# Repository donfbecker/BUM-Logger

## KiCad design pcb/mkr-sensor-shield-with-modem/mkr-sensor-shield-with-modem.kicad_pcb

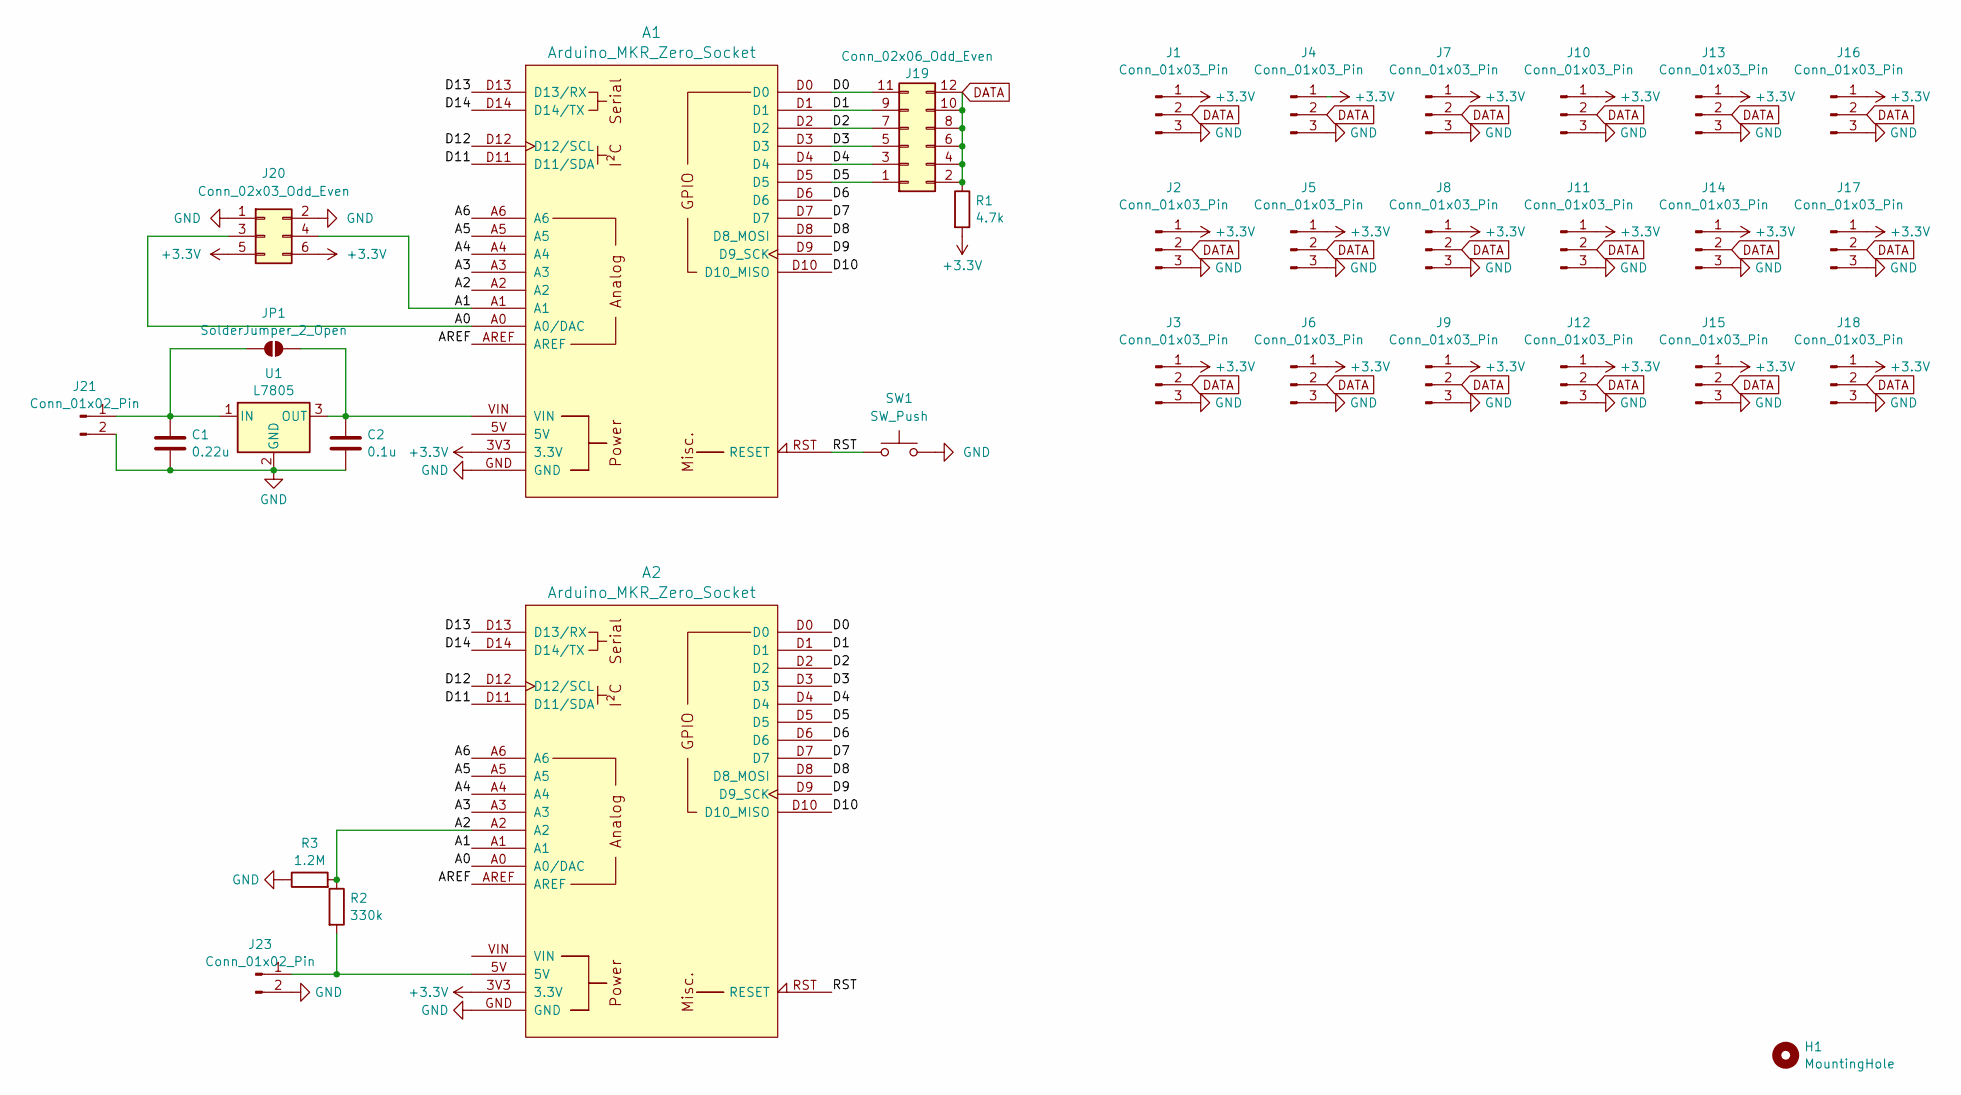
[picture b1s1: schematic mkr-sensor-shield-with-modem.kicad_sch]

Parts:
A1, A2: Arduino_MKR_Zero_Socket
C1: 0.22u; C_1206_3216Metric
C2: 0.1u; C_1206_3216Metric
H1: MountingHole; MountingHole_4.3mm_M4
J1, J2, J3, J4, J5, J6, J7, J8, J9, J10, J11, J12, J13, J14, J15, J16, J17, J18: Conn_01x03_Pin; JST_XH_B3B-XH-A_1x03_P2.50mm_Vertical
J19: Conn_02x06_Odd_Even; PinHeader_2x06_P2.54mm_Vertical
J20: Conn_02x03_Odd_Even; PinHeader_2x03_P2.54mm_Vertical
J21, J23: Conn_01x02_Pin; Power_Solder_Pads
JP1: SolderJumper_2_Open; SolderJumper-2_P1.3mm_Open_TrianglePad1.0x1.5mm
R1: 4.7k; R_Axial_DIN0207_L6.3mm_D2.5mm_P10.16mm_Horizontal
R2: 330k; R_Axial_DIN0207_L6.3mm_D2.5mm_P10.16mm_Horizontal
R3: 1.2M; R_Axial_DIN0207_L6.3mm_D2.5mm_P10.16mm_Horizontal
SW1: SW_Push; SW_PUSH_6mm
U1: L7805; SOT-223

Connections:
+3.3V: A1.3V3 (3.3V), A2.3V3 (3.3V), J1.1, J2.1, J3.1, J4.1, J5.1, J6.1, J7.1, J8.1, J9.1, J10.1, J11.1, J12.1, J13.1, J14.1, J15.1, J16.1, J17.1, J18.1, J20.5, J20.6, R1.2
/A0: A1.A0 (A0/DAC), A2.A0 (A0/DAC), J20.3
/A1: A1.A1, A2.A1, J20.4
/A2: A1.A2, A2.A2, R2.1, R3.2
/A3: A1.A3, A2.A3
/A4: A1.A4, A2.A4
/A5: A1.A5, A2.A5
/A6: A1.A6, A2.A6
/AREF: A1.AREF, A2.AREF
/D0: A1.D0, A2.D0, J19.11
/D1: A1.D1, A2.D1, J19.9
/D2: A1.D2, A2.D2, J19.7
/D3: A1.D3, A2.D3, J19.5
/D4: A1.D4, A2.D4, J19.3
/D5: A1.D5, A2.D5, J19.1
/D6: A1.D6, A2.D6
/D7: A1.D7, A2.D7
/D8: A1.D8 (D8_MOSI), A2.D8 (D8_MOSI)
/D9: A1.D9 (D9_SCK), A2.D9 (D9_SCK)
/D10: A1.D10 (D10_MISO), A2.D10 (D10_MISO)
/D11: A1.D11 (D11/SDA), A2.D11 (D11/SDA)
/D12: A1.D12 (D12/SCL), A2.D12 (D12/SCL)
/D13: A1.D13 (D13/RX), A2.D13 (D13/RX)
/D14: A1.D14 (D14/TX), A2.D14 (D14/TX)
/RST: A1.RST (RESET), A2.RST (RESET), SW1.1
DATA: J1.2, J2.2, J3.2, J4.2, J5.2, J6.2, J7.2, J8.2, J9.2, J10.2, J11.2, J12.2, J13.2, J14.2, J15.2, J16.2, J17.2, J18.2, J19.2, J19.4, J19.6, J19.8, J19.10, J19.12, R1.1
GND: A1.GND, A2.GND, C1.2, C2.2, J1.3, J2.3, J3.3, J4.3, J5.3, J6.3, J7.3, J8.3, J9.3, J10.3, J11.3, J12.3, J13.3, J14.3, J15.3, J16.3, J17.3, J18.3, J20.1, J20.2, J21.2, J23.2, R3.1, SW1.2, U1.2 (GND)
unnamed: C1.1, J21.1, JP1.1 (A), U1.1 (IN)
unnamed: A2.5V, J23.1, R2.2
unnamed: A1.VIN, C2.1, JP1.2 (B), U1.3 (OUT)

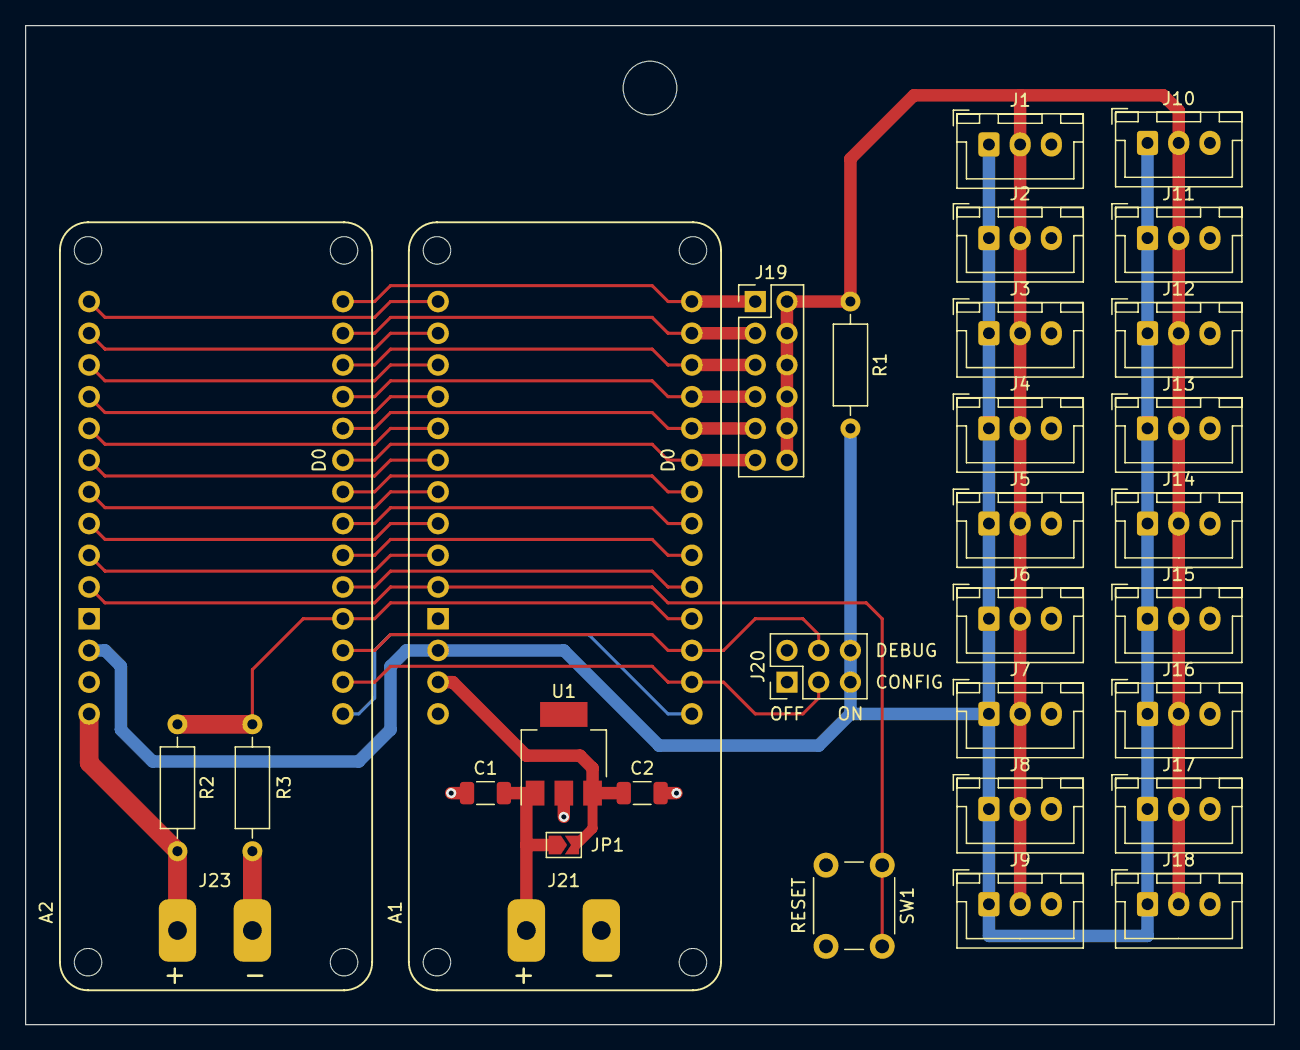
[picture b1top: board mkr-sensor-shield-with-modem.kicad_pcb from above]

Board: 2 copper layers, 100.0 x 80.0 mm, 33 parts (0 on the bottom side), 30 nets.

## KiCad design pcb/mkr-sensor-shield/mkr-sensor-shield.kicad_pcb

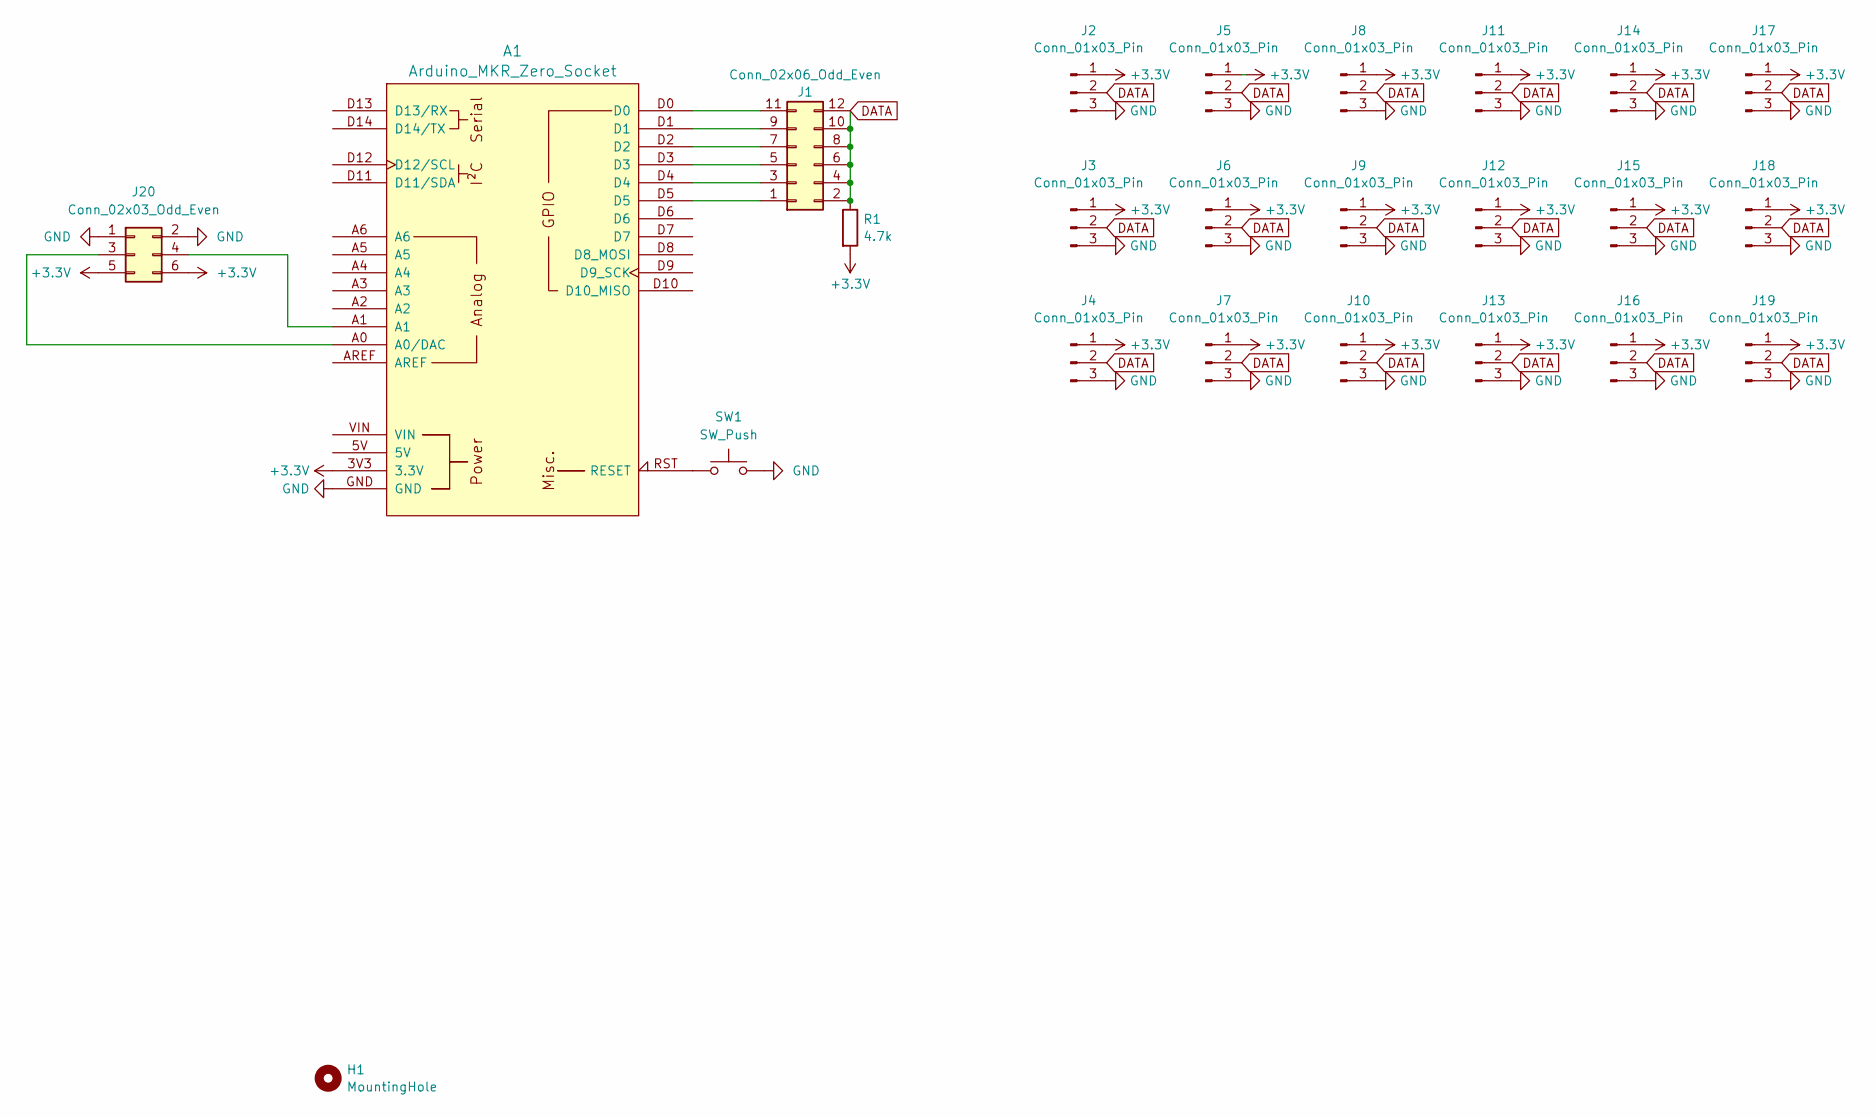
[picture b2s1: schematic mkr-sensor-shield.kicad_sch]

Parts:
A1: Arduino_MKR_Zero_Socket
H1: MountingHole; MountingHole_4.3mm_M4
J1: Conn_02x06_Odd_Even; PinHeader_2x06_P2.54mm_Vertical
J2, J3, J4, J5, J6, J7, J8, J9, J10, J11, J12, J13, J14, J15, J16, J17, J18, J19: Conn_01x03_Pin; JST_XH_B3B-XH-A_1x03_P2.50mm_Vertical
J20: Conn_02x03_Odd_Even; PinHeader_2x03_P2.54mm_Vertical
R1: 4.7k; R_Axial_DIN0207_L6.3mm_D2.5mm_P10.16mm_Horizontal
SW1: SW_Push; SW_PUSH_6mm

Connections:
+3.3V: A1.3V3 (3.3V), J2.1, J3.1, J4.1, J5.1, J6.1, J7.1, J8.1, J9.1, J10.1, J11.1, J12.1, J13.1, J14.1, J15.1, J16.1, J17.1, J18.1, J19.1, J20.5, J20.6, R1.2
DATA: J1.2, J1.4, J1.6, J1.8, J1.10, J1.12, J2.2, J3.2, J4.2, J5.2, J6.2, J7.2, J8.2, J9.2, J10.2, J11.2, J12.2, J13.2, J14.2, J15.2, J16.2, J17.2, J18.2, J19.2, R1.1
GND: A1.GND, J2.3, J3.3, J4.3, J5.3, J6.3, J7.3, J8.3, J9.3, J10.3, J11.3, J12.3, J13.3, J14.3, J15.3, J16.3, J17.3, J18.3, J19.3, J20.1, J20.2, SW1.2
unnamed: A1.A0 (A0/DAC), J20.3
unnamed: A1.RST (RESET), SW1.1
unnamed: A1.D5, J1.1
unnamed: A1.D4, J1.3
unnamed: A1.D3, J1.5
unnamed: A1.D2, J1.7
unnamed: A1.D1, J1.9
unnamed: A1.D0, J1.11
unnamed: A1.A1, J20.4

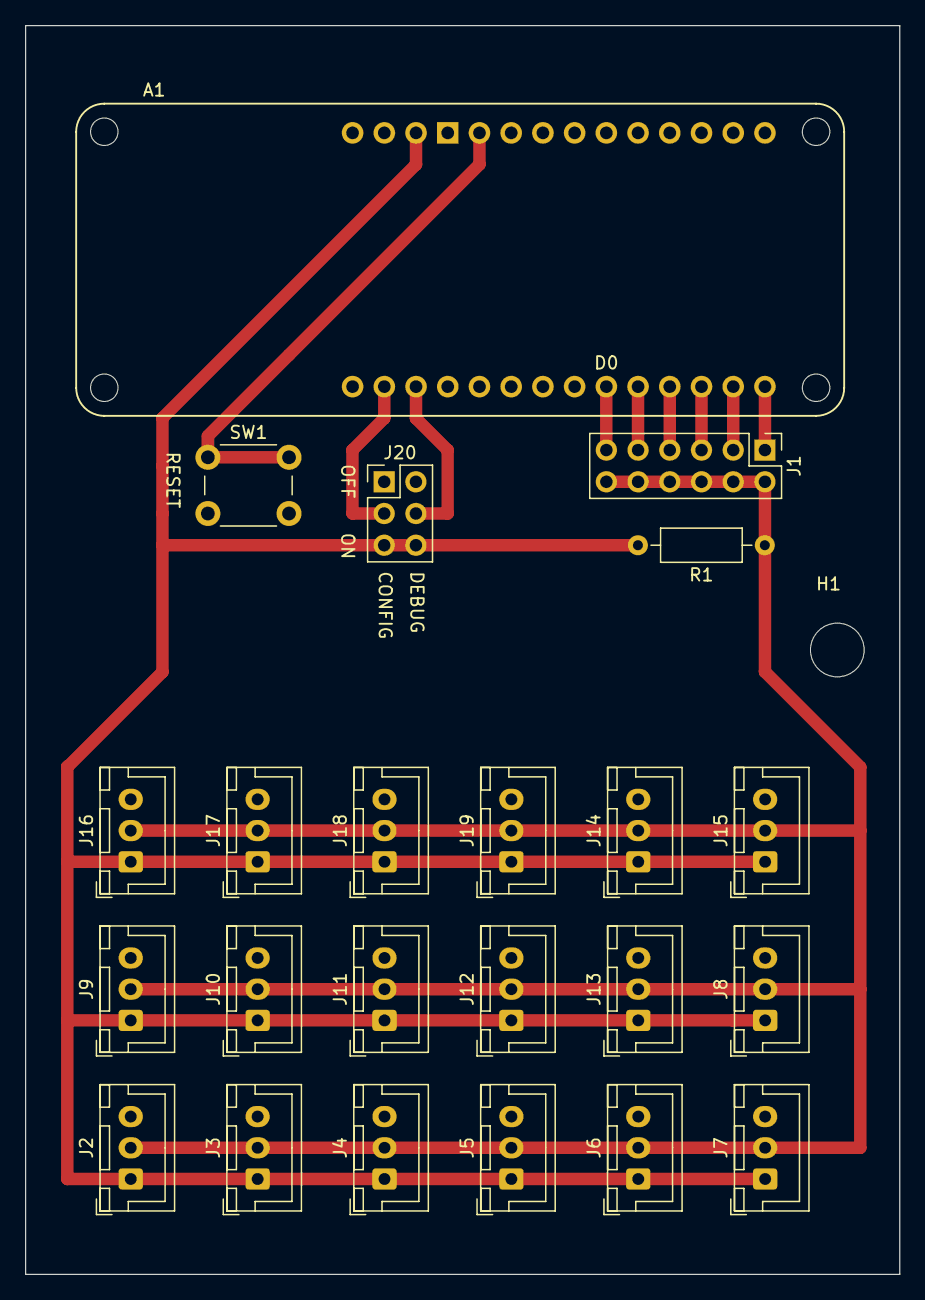
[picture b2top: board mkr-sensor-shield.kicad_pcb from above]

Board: 2 copper layers, 70.0 x 100.0 mm, 24 parts (0 on the bottom side), 12 nets.

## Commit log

2024-02-15 Initial import
2024-02-15 Fix capitalization to match repo on GitHub
2024-02-24 All GSM support
2024-03-21 Add support for monitoring second battery, and logging the value. Fix modem not working after deep sleep. Fix sensorCount value when removing sensors
2024-03-21 Add KiCad PCB files
2024-03-31 Add GSM Timeout configuration value. Add Lux sensor
2024-06-23 Add dumplog command
2025-12-06 Remove backups from repo. Add jumper to bypass voltage regulator
